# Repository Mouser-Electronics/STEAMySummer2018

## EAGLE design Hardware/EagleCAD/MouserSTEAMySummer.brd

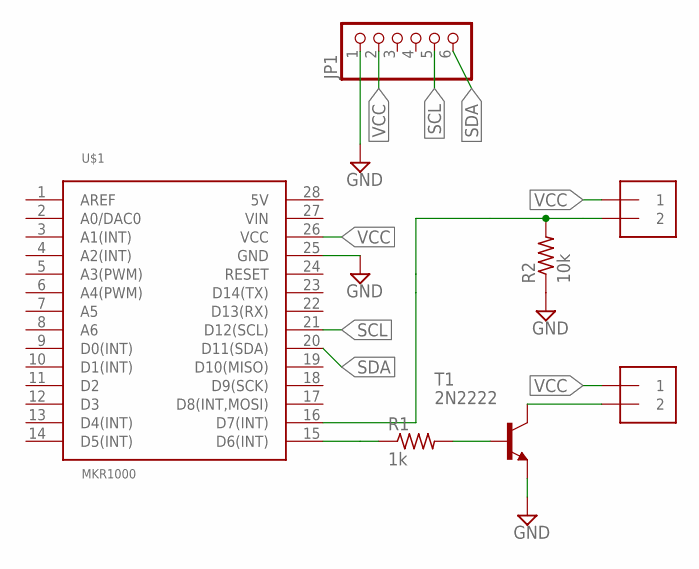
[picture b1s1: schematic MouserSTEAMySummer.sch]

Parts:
BUZZER: 1X2-3.5MM
J1: 1X2-3.5MM
JP1: PINHD-1X6B; 1X06-BIG
R1: 1k; 0207/7
R2: 10k; 0207/7
T1: 2N2222; TO92-EBC-OVAL
U$1: MKR1000; MKR1000-SOCKET

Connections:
GND: JP1.1, R2.1, T1.E, U$1.25 (GND)
unnamed: R1.1, U$1.15 (D6(INT))
unnamed: R1.2, T1.B
unnamed: BUZZER.2, T1.C
unnamed: J1.2, R2.2, U$1.16 (D7(INT))
SCL: JP1.5, U$1.21 (D12(SCL))
SDA: JP1.6, U$1.20 (D11(SDA))
VCC: BUZZER.1, J1.1, JP1.2, U$1.26 (VCC)

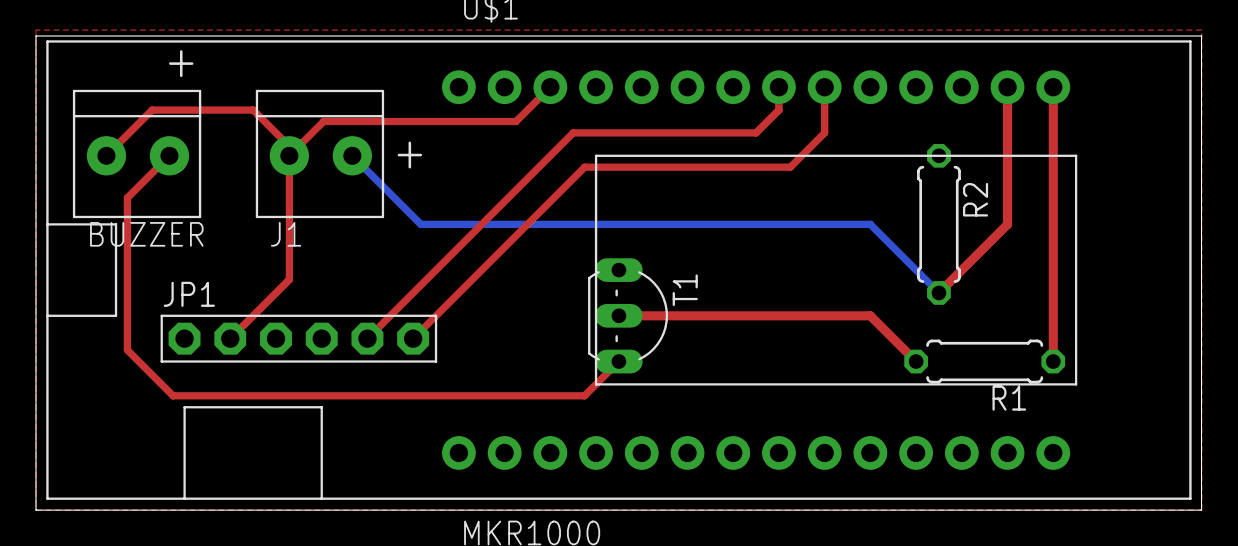
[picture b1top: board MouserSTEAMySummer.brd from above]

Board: 2 copper layers, 64.8 x 26.3 mm, 7 parts (0 on the bottom side), 8 nets.

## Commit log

2018-07-09 init commit
